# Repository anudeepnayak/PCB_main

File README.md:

# PCB_main

Schematic and Layout for Maxon motor, Arduino and a few other sensors.

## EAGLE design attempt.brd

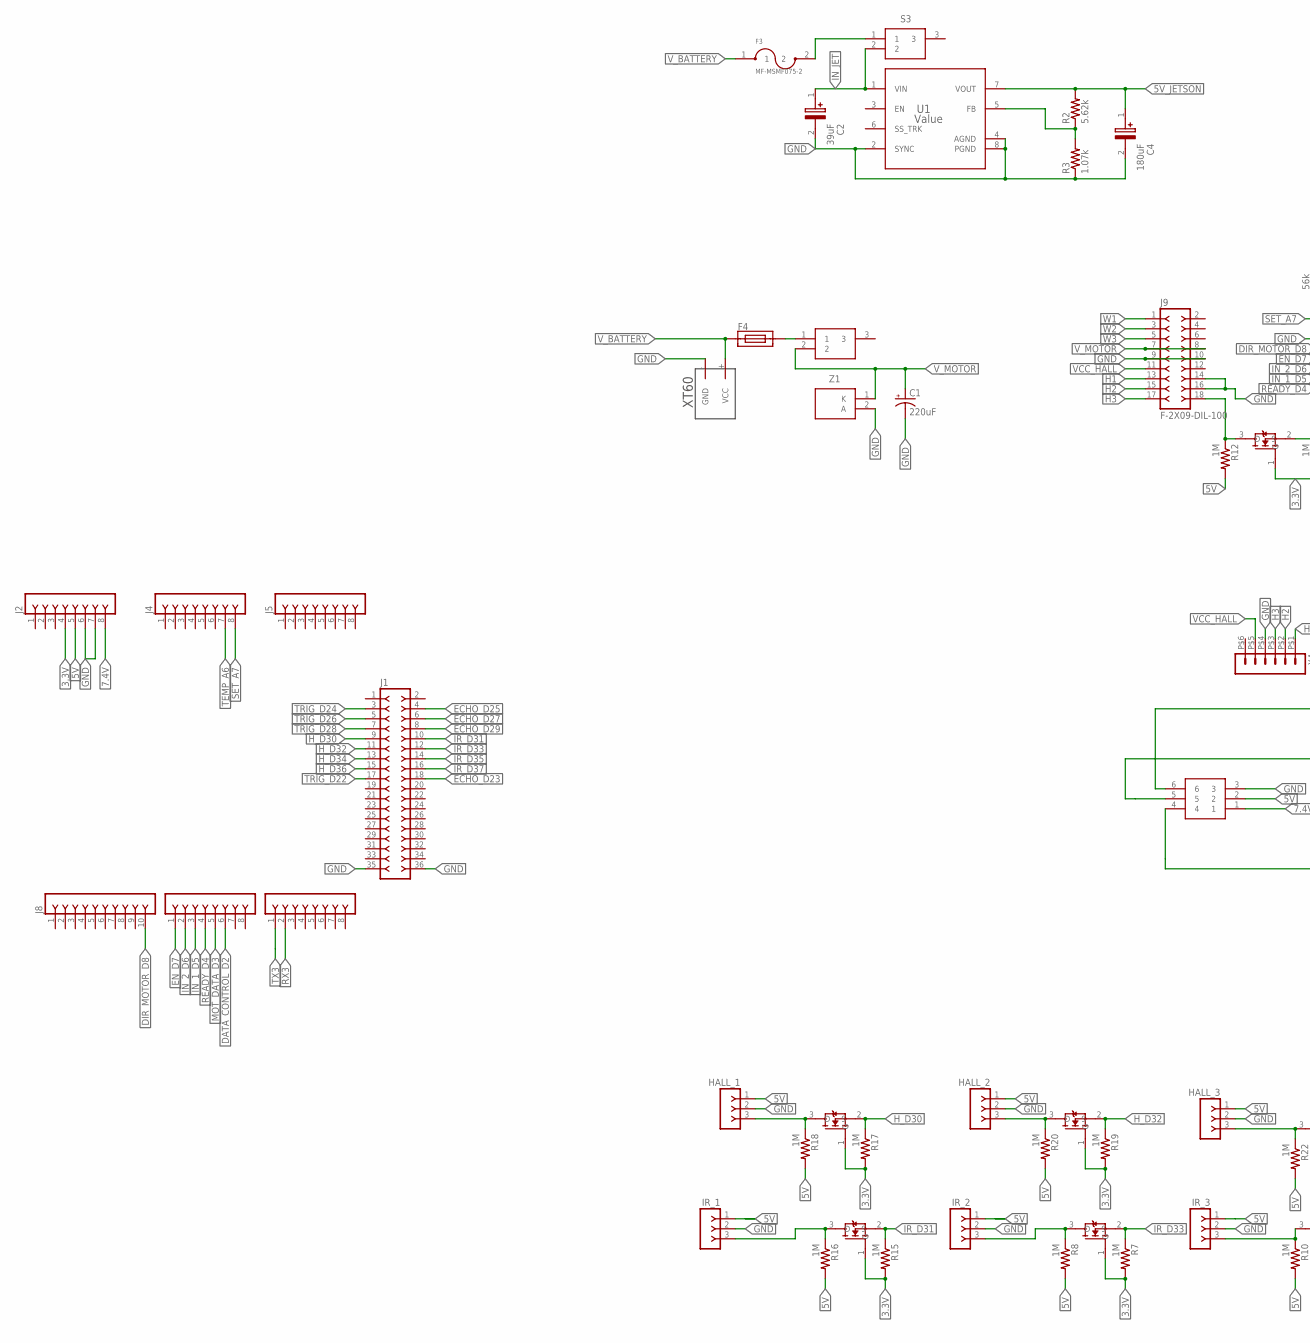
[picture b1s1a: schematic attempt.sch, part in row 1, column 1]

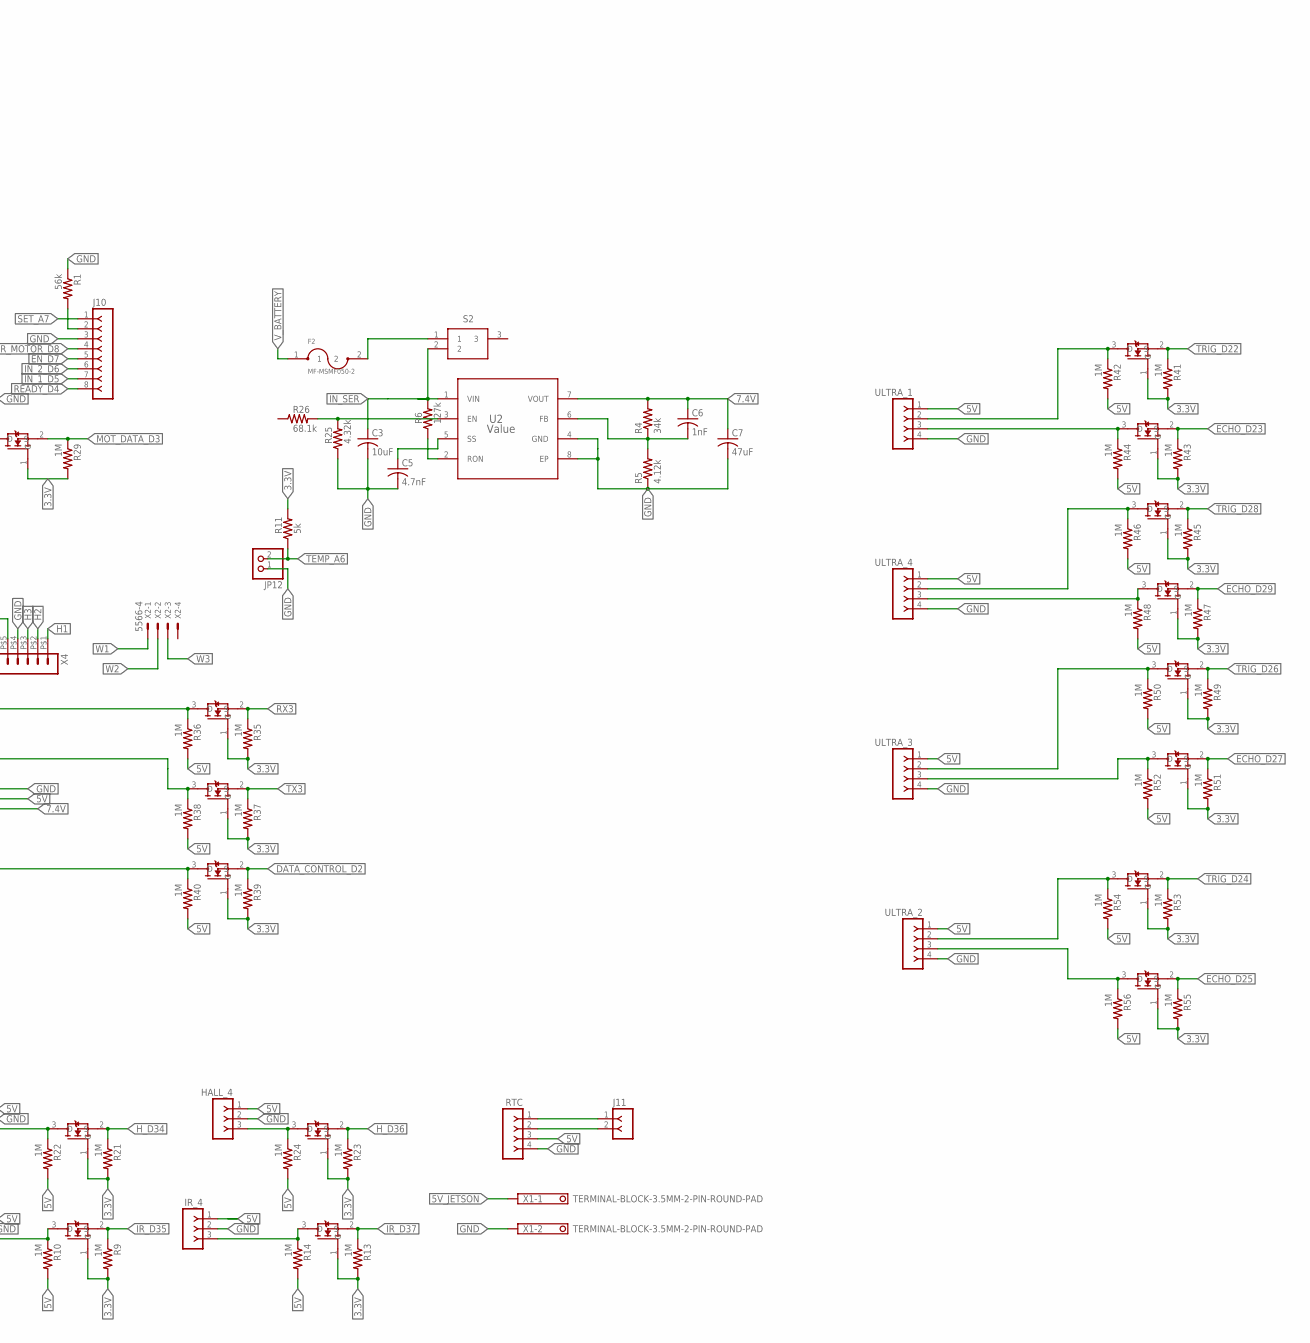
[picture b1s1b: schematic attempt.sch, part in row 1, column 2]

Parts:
C1: 220uF; CPOL-RADIAL-2.5MM-6.5MM; MPN 35ZLH220MEFC8X11.5
C2: 39uF; CAPAE830X700N
C3: 10uF; C0805; MPN 06035C472KAT2A
C4: 180uF; CAPAE830X700N
C5: 4.7nF; C0805; MPN 06035C472KAT2A
C6: 1nF; C0805; MPN 04025C102KAT2A
C7: 47uF; C0805; MPN 06035C472KAT2A
F2: MF-MSMF050-2; MF-MSMF050-2_FUSM4632X85; MPN MF-MSMF050-2
F3: MF-MSMF075-2; FUSM4632X85; MPN MF-MSMF075/24-2
F4: SMF_OMNIBLOK_154.062; NANO2_SMF_FUSEBLOCK
HALL_1, HALL_2, HALL_3, HALL_4: F-1X03-SIP-100-32; SIP-100-03-32
IR_1, IR_2, IR_3, IR_4: F-1X03-SIP-100-32; SIP-100-03-32
J1: F-2X18-DIL-100; DIL-100-2X18
J2, J4, J5, J6, J7, J10: F-1X08-SIP-100-32; SIP-100-08-32
J3: 53375-0610; MPN 53375-0610
J8: F-1X10-SIP-100-32; SIP-100-10-32
J9: F-2X09-DIL-100; DIL-100-2X09
J11: F-1X02-SIP-100-32; SIP-100-02-32
JP12: PINHD-1X2; 1X02
Q1, Q2, Q3, Q4, Q5, Q6, Q7, Q8, Q9, Q15, Q16, Q17, Q18, Q19, Q20, Q21, Q22, Q23, Q24, Q25: BSS138; BSS138_SOT95P240X120-3N; MPN BSS138LT1G
R1: 56k; R0805; MPN MCWR08X5602FTL
R2: 5.62k; R0805; MPN CRCW08055K62FKEA
R3: 1.07k; R0805; MPN ERJ6ENF1071V
R4: 34k; R0805; MPN MCMR08X3402FTL
R5: 4.12k; R0805; MPN CRCW08054K12FKEA.
R6: 127k; R0805; MPN ERJ6ENF1273V
R7, R8, R9, R10, R12, R13, R14, R15, R16, R17, R18, R19, R20, R21, R22, R23, R24, R29, R35, R36, R37, R38, R39, R40, R41, R42, R43, R44, R45, R46, R47, R48, R49, R50, R51, R52, R53, R54, R55, R56: 1M; R0805; MPN MCWR08X1004FTL
R11: 5k; R0805; MPN CRCW08051K50FKEA
R25: 4.32k; R0805; MPN ERJ6ENF1273V
R26: 68.1k; R0805; MPN ERJ6ENF1273V
RTC: F-1X04-SIP-100-32; SIP-100-04-32
S1, S2, S3: E101SYZQE; E105MD9V3GE
U1, U2: Value; NDW0007A
U$1: XT60
ULTRA_1, ULTRA_2, ULTRA_3, ULTRA_4: F-1X04-SIP-100-32; SIP-100-04-32
X1: TERMINAL-BLOCK-3.5MM-2-PIN-ROUND-PAD; TERMINAL-BLOCK-2-PIN-3.5MM-ROUND-PAD
X2: 5566-4
X4: HEADER_POS6_43045-0600; 43045-0600; MPN 43045-0600
Z1: MMSZ5256B-13-F; SOD3716X145N

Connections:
3.3V: J2.4, Q1.1 (G), Q2.1 (G), Q3.1 (G), Q4.1 (G), Q5.1 (G), Q6.1 (G), Q7.1 (G), Q8.1 (G), Q9.1 (G), Q15.1 (G), Q16.1 (G), Q17.1 (G), Q18.1 (G), Q19.1 (G), Q20.1 (G), Q21.1 (G), Q22.1 (G), Q23.1 (G), Q24.1 (G), Q25.1 (G), R7.2, R9.2, R11.2, R13.2, R15.2, R17.2, R19.2, R21.2, R23.2, R29.2, R35.2, R37.2, R39.2, R41.2, R43.2, R45.2, R47.2, R49.2, R51.2, R53.2, R55.2
5V: HALL_1.1, HALL_2.1, HALL_3.1, HALL_4.1, IR_1.1, IR_2.1, IR_3.1, IR_4.1, J2.5, J3.2, R8.2, R10.2, R12.2, R14.2, R16.2, R18.2, R20.2, R22.2, R24.2, R36.2, R38.2, R40.2, R42.2, R44.2, R46.2, R48.2, R50.2, R52.2, R54.2, R56.2, RTC.3, ULTRA_1.1, ULTRA_2.1, ULTRA_3.1, ULTRA_4.1
5V_JETSON: C4.1 (+), R2.2, U1.7 (VOUT), X1.1
7.4V: C6.1, C7.1, J2.8, J3.1, R4.2, U2.7 (VOUT)
DATA_CONTROL_D2: J6.6, Q17.2 (S), R39.1
DIR_MOTOR_D8: J8.10, J10.4
ECHO_D23: J1.18, Q19.2 (S), R43.1
ECHO_D25: J1.4, Q25.2 (S), R55.1
ECHO_D27: J1.6, Q23.2 (S), R51.1
ECHO_D29: J1.8, Q21.2 (S), R47.1
EN_D7: J6.1, J10.5
GND: C1.2 (-), C2.2 (-), C3.2, C4.2 (-), C5.2, C7.2, HALL_1.2, HALL_2.2, HALL_3.2, HALL_4.2, IR_1.2, IR_2.2, IR_3.2, IR_4.2, J1.35, J1.36, J2.6, J2.7, J3.3, J9.9, J9.10, J9.14, J9.16, J10.3, JP12.1, R1.1, R3.1, R5.1, R25.1, RTC.4, U1.2 (SYNC), U1.4 (AGND), U1.8 (PGND), U2.4 (GND), U2.8 (EP), U$1.- (GND), ULTRA_1.4, ULTRA_2.4, ULTRA_3.4, ULTRA_4.4, X1.2, X4.P$4 (4), Z1.2 (A)
H1: J9.13, X4.P$1 (1)
H2: J9.15, X4.P$2 (2)
H3: J9.17, X4.P$3 (3)
H_D30: J1.9, Q6.2 (S), R17.1
H_D32: J1.11, Q7.2 (S), R19.1
H_D34: J1.13, Q8.2 (S), R21.1
H_D36: J1.15, Q9.2 (S), R23.1
IN_1_D5: J6.3, J10.7
IN_2_D6: J6.2, J10.6
IN_JET: C2.1 (+), S3.2, U1.1 (VIN)
IN_SER: C3.1, R6.2, S2.2, U2.1 (VIN)
IR_D31: J1.10, Q5.2 (S), R15.1
IR_D33: J1.12, Q1.2 (S), R7.1
IR_D35: J1.14, Q2.2 (S), R9.1
IR_D37: J1.16, Q4.2 (S), R13.1
MOT_DATA_D3: J6.5, Q3.2 (S), R29.1
unnamed: F4.2, S1.1
unnamed: IR_1.3, Q5.3 (D), R16.1
unnamed: R2.1, R3.2, U1.5 (FB)
unnamed: F2.2, S2.1
unnamed: HALL_1.3, Q6.3 (D), R18.1
unnamed: C5.1, U2.5 (SS)
unnamed: IR_2.3, Q1.3 (D), R8.1
unnamed: C6.2, R4.1, R5.2, U2.6 (FB)
unnamed: Q18.3 (D), R42.1, ULTRA_1.2
unnamed: R6.1, U2.2 (RON)
unnamed: Q19.3 (D), R44.1, ULTRA_1.3
unnamed: IR_3.3, Q2.3 (D), R10.1
unnamed: J11.1, RTC.1
unnamed: J11.2, RTC.2
unnamed: HALL_2.3, Q7.3 (D), R20.1
unnamed: IR_4.3, Q4.3 (D), R14.1
unnamed: J3.6, Q15.3 (D), R36.1
unnamed: Q20.3 (D), R46.1, ULTRA_4.2
unnamed: HALL_3.3, Q8.3 (D), R22.1
unnamed: Q21.3 (D), R48.1, ULTRA_4.3
unnamed: Q22.3 (D), R50.1, ULTRA_3.2
unnamed: Q23.3 (D), R52.1, ULTRA_3.3
unnamed: Q24.3 (D), R54.1, ULTRA_2.2
unnamed: HALL_4.3, Q9.3 (D), R24.1
unnamed: J10.2, R1.2
unnamed: J3.5, Q16.3 (D), R38.1
unnamed: Q25.3 (D), R56.1, ULTRA_2.3
unnamed: R25.2, R26.2, U2.3 (EN)
unnamed: J3.4, Q17.3 (D), R40.1
unnamed: J9.18, Q3.3 (D), R12.1
unnamed: F3.2, S3.1
READY_D4: J6.4, J10.8
RX3: J7.2, Q15.2 (S), R35.1
SET_A7: J4.8, J10.1
TEMP_A6: J4.7, JP12.2, R11.1
TRIG_D22: J1.17, Q18.2 (S), R41.1
TRIG_D24: J1.3, Q24.2 (S), R53.1
TRIG_D26: J1.5, Q22.2 (S), R49.1
TRIG_D28: J1.7, Q20.2 (S), R45.1
TX3: J7.1, Q16.2 (S), R37.1
VCC_HALL: J9.11, X4.P$5 (5)
V_BATTERY: F2.1, F3.1, F4.1, U$1.+ (VCC)
V_MOTOR: C1.1 (+), J9.7, J9.8, S1.2, Z1.1 (K)
W1: J9.1, X2.1
W2: J9.3, X2.2
W3: J9.5, X2.3

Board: 2 copper layers, 114 parts (0 on the bottom side), 74 nets, no tracks yet.

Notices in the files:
parts and their libraries:
con-headers-jp: Copyright (C) 2008, Bob Starr
SparkFun-Capacitors: Licensing: Creative Commons ShareAlike 4.0 International - https://creativecommons.org/licenses/by-sa/4.0
